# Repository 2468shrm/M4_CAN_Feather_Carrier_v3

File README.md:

# M4_CAN_Feather_Carrier_v3

## Board Layout

## Changes from V2

The changes from [V2](https://github.com/2468shrm/M4_CAN_Feather_Carrier_v2) of this
board are largely layout/component positioning. The following
are the changes:
- DIO voltage selector jumper changed pin assignments
- All stake headers are moved to the same edge of the board (bottom edge). It still selects between 5V and 3.3V.
- All STEMMA QT/QWIIC connectors are moved to the same edge of the board (right edge).
- Screw terminals for power and NEOPIXEL are replaced with WAGO 250-series connectors. These are the same connectors used in REV products (CAN, low-current power, etc.).
- The board size changed to 64 x 52 mm.
- The mounting holes are consistently 3 mm from their respective edges.
- The orientation of the ICs (level shifter and analog buffer) are in the same orientation.

Other than that, there are minor changes to make assembly simpler.  Primarily this includes
changing the two ICs so that pin 1 is in the same orientation (V2 had pin 1 pointing in
oppposite directions and sometimes one might forget).

A PDF copy of the schematic [here](https://github.com/2468shrm/M4_CAN_Feather_Carrier_v3/blob/main/Images/Schematic.pdf).

## Checkout Status

This board was fabbed at JLCPCB during the week of 30 Jan, 2023 and articles received
(plus solder stencil). One article has been assembled and the following has been tested:
- Power input filter
- 5V supply
- X1 (I2C/STEMMA QR/QWIIC) interface
- NeoPixel interface

Not yet tested:
- X2-X4
- Level shifter and DIO interface
- Analog buffer and AI interface

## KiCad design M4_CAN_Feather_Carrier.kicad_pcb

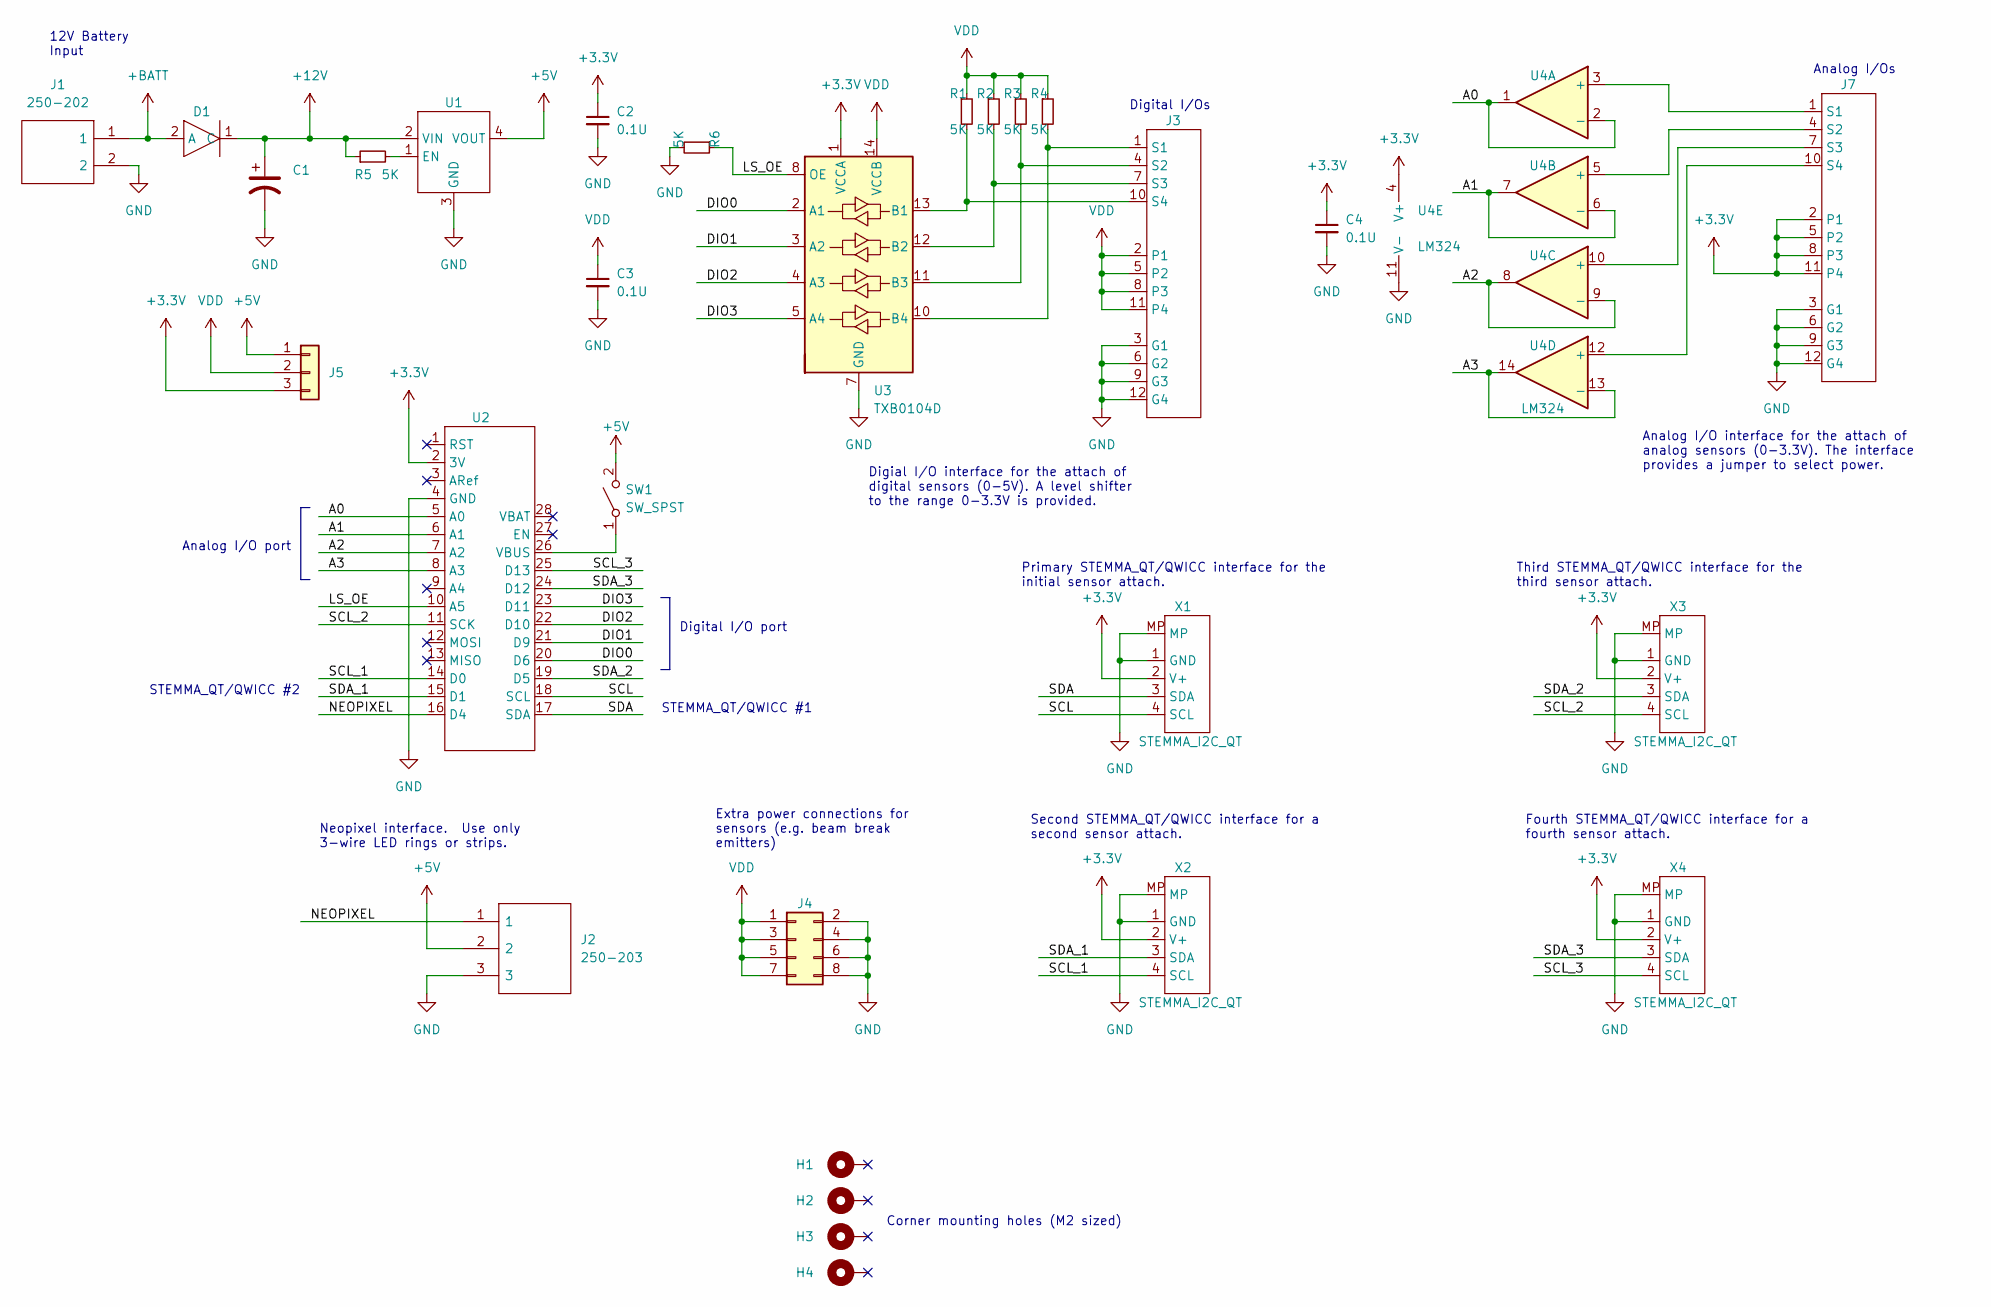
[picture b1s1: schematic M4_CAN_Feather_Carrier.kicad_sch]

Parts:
C1: 10u; CP_Elec_8x10
C2, C3, C4: 0.1U; C_0805_2012Metric
D1: UPR20e3; DO-216
H1, H2, H3, H4: MountingHole_Pad; MountingHole_2.2mm_M2_DIN965_Pad
J1: 250-202; 250202; Manufacturer_Part_Number 250-202
J2: 250-203; 250-203_1; Manufacturer_Part_Number 250-203
J3, J7: conn_04_03; conn_04x03
J4: Conn_02x04_Odd_Even; PinHeader_2x04_P2.54mm_Vertical
J5: Conn_01x03; PinHeader_1x03_P2.54mm_Vertical
R1, R2, R3, R4, R5, R6: 5K; R_0805_2012Metric
SW1: SW_SPST; SPST-KJ01
U1: Weewooday-820
U2: Feather_M4_CAN_Express
U3: TXB0104D; SOIC-14_3.9x8.7mm_P1.27mm
U4: LM324; SOIC-14_3.9x8.7mm_P1.27mm
X1, X2, X3, X4: STEMMA_I2C_QT; JST_SH_SM04B-SRSS-TB_1x04-1MP_P1.00mm_Horizontal

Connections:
+3.3V: C2.1, C4.1, J5.3, J7.2 (P1), J7.5 (P2), J7.8 (P3), J7.11 (P4), U2.2 (3V), U3.1 (VCCA), U4.4 (V+), X1.2 (V+), X2.2 (V+), X3.2 (V+), X4.2 (V+)
+5V: J2.2, J5.1, SW1.2 (B), U1.4 (VOUT)
+12V: C1.1, D1.1 (C), R5.1, U1.2 (VIN)
+BATT: D1.2 (A), J1.1
/A0: U2.5 (A0), U4.1, U4.2 (-)
/A1: U2.6 (A1), U4.6 (-), U4.7
/A2: U2.7 (A2), U4.8, U4.9 (-)
/A3: U2.8 (A3), U4.13 (-), U4.14
/DIO0: U2.20 (D6), U3.2 (A1)
/DIO1: U2.21 (D9), U3.3 (A2)
/DIO2: U2.22 (D10), U3.4 (A3)
/DIO3: U2.23 (D11), U3.5 (A4)
/LS_OE: R6.1, U2.10 (A5), U3.8 (OE)
/NEOPIXEL: J2.1, U2.16 (D4)
/SCL: U2.18 (SCL), X1.4 (SCL)
/SCL_1: U2.14 (D0), X2.4 (SCL)
/SCL_2: U2.11 (SCK), X3.4 (SCL)
/SCL_3: U2.25 (D13), X4.4 (SCL)
/SDA: U2.17 (SDA), X1.3 (SDA)
/SDA_1: U2.15 (D1), X2.3 (SDA)
/SDA_2: U2.19 (D5), X3.3 (SDA)
/SDA_3: U2.24 (D12), X4.3 (SDA)
GND: C1.2, C2.2, C3.2, C4.2, J1.2, J2.3, J3.3 (G1), J3.6 (G2), J3.9 (G3), J3.12 (G4), J4.2, J4.4, J4.6, J4.8, J7.3 (G1), J7.6 (G2), J7.9 (G3), J7.12 (G4), R6.2, U1.3 (GND), U2.4 (GND), U3.7 (GND), U4.11 (V-), X1.1 (GND), X1.MP, X2.1 (GND), X2.MP, X3.1 (GND), X3.MP, X4.1 (GND), X4.MP
unnamed: J3.1 (S1), R4.2, U3.10 (B4)
unnamed: J3.4 (S2), R3.2, U3.11 (B3)
unnamed: J3.7 (S3), R2.2, U3.12 (B2)
unnamed: J3.10 (S4), R1.2, U3.13 (B1)
unnamed: J7.1 (S1), U4.3 (+)
unnamed: J7.4 (S2), U4.5 (+)
unnamed: J7.7 (S3), U4.10 (+)
unnamed: J7.10 (S4), U4.12 (+)
unnamed: R5.2, U1.1 (EN)
unnamed: SW1.1 (A), U2.26 (VBUS)
VDD: C3.1, J3.2 (P1), J3.5 (P2), J3.8 (P3), J3.11 (P4), J4.1, J4.3, J4.5, J4.7, J5.2, R1.1, R2.1, R3.1, R4.1, U3.14 (VCCB)

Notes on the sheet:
Corner mounting holes (M2 sized)
Digital I/Os
Analog I/Os
Third STEMMA_QT/QWICC interface for the third sensor attach.
Primary STEMMA_QT/QWICC interface for the initial sensor attach.
Extra power connections for sensors (e.g. beam break emitters)
Digial I/O interface for the attach of digital sensors (0-5V). A level shifter to the range 0-3.3V is provided.
Second STEMMA_QT/QWICC interface for a second sensor attach.
Digital I/O port
Analog I/O port
STEMMA_QT/QWICC #1
12V Battery Input
STEMMA_QT/QWICC #2
Analog I/O interface for the attach of analog sensors (0-3.3V). The interface provides a jumper to select power.
Neopixel interface. Use only 3-wire LED rings or strips.
Fourth STEMMA_QT/QWICC interface for a fourth sensor attach.

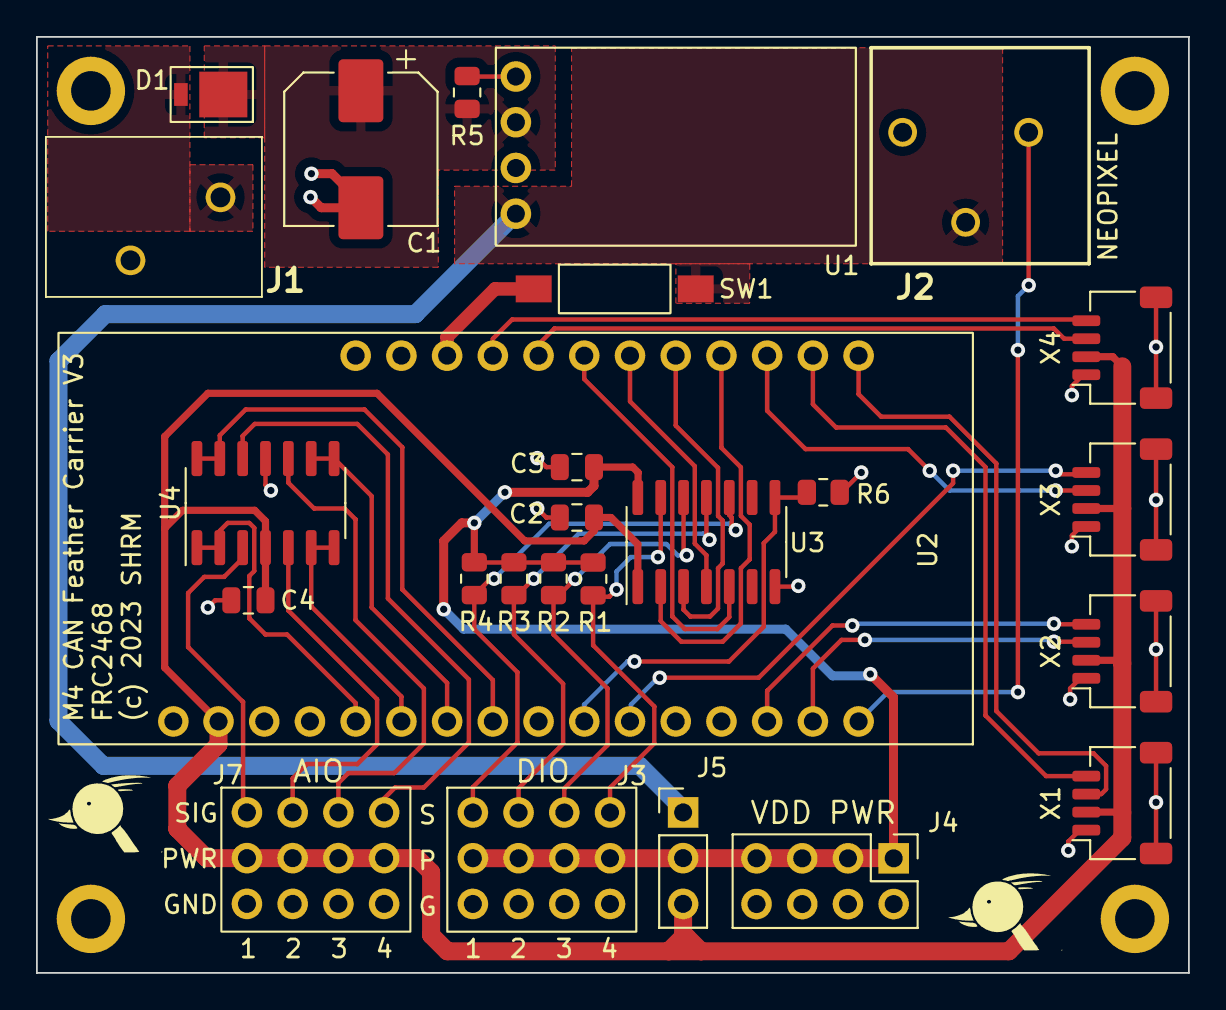
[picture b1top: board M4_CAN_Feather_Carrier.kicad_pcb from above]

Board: 2 copper layers, 64.0 x 52.0 mm, 30 parts (0 on the bottom side), 34 nets.

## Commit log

2023-01-30 KiCAD files
2023-01-30 Gerber files & zip as uploaded to PCB manufacturer
2023-01-30 added PCB image
2023-02-15 add schematic to images
2023-02-15 marginally better detail
2023-02-15 marginally better detail about testing status

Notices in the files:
M4_CAN_Feather_Carrier.kicad_pcb:
(c) 2023 SHRM
